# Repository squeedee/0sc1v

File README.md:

# 0sc1v
Turn the fader board from a Yamaha 01v mixer into a compact OSC controller

The [Yamaha 01v](https://usa.yamaha.com/files/download/other_assets/0/320870/01VE.pdf) was my favorite digital mixer of the 90s.
However I recently upgraded, to the [X-Air Xr-18 by Behringer](https://www.musictribe.com/Categories/Behringer/Mixers/Digital/XR18/p/P0BI8).
The XR-18 is so cheap, does so much, and I chose it based on certain criteria:

1. 24bit for headroom, the 16bit 01v made me work too hard up front
2. Lots of digital in/outs to my PC. I would have been happy with 8/8, but the XR-18 comes with 18/18
3. Physical controls

And it's the last point that makes the XR-18 sad for me, I like having physical faders. So this project is all about using
the motorized faders of my ailing 01v as a Fader Controller for the XR-18 (and everything else)

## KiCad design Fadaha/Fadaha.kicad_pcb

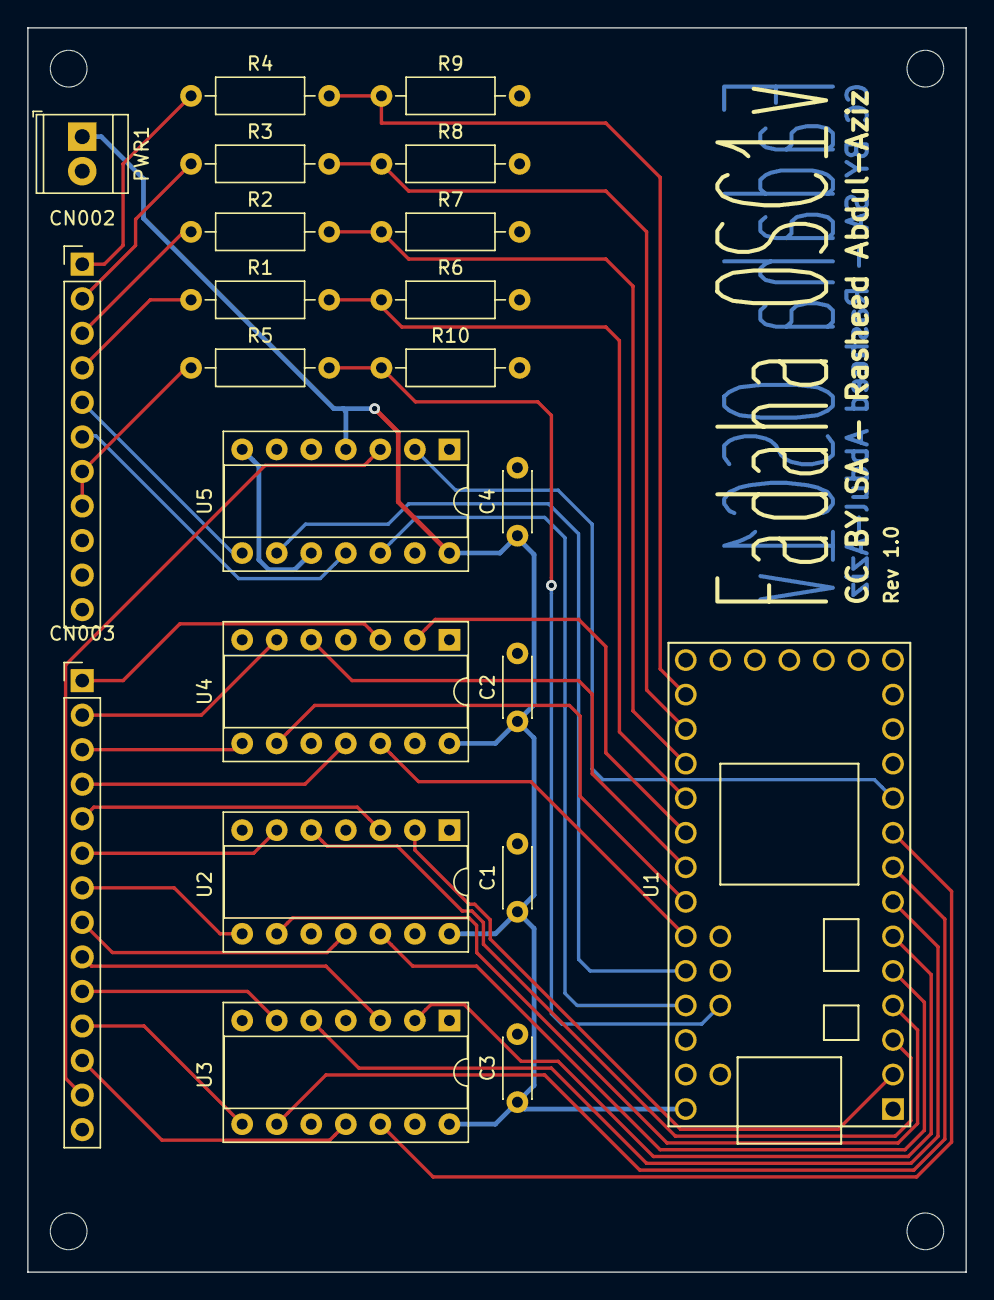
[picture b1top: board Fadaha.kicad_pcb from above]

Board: 2 copper layers, 69.0 x 91.5 mm, 23 parts (0 on the bottom side), 42 nets.

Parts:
C1, C2, C3, C4: 100nf; C_Disc_D4.3mm_W1.9mm_P5.00mm
CN002: 11 pin header; PinHeader_1x11_P2.54mm_Vertical
CN003: 14 pin header; PinHeader_1x14_P2.54mm_Vertical
GND: MountingHole_2.7mm_M2.5
PWR1: Screw_Terminal_01x02; TerminalBlock_TE_282834-2_1x02_P2.54mm_Horizontal
R1, R2, R3, R4, R5: 11k; R_Axial_DIN0207_L6.3mm_D2.5mm_P10.16mm_Horizontal
R6, R7, R8, R9, R10: 20k; R_Axial_DIN0207_L6.3mm_D2.5mm_P10.16mm_Horizontal
U1: Teensy3.2; Teensy30_31_32_LC-custom
U2, U3, U4, U5: 74125; DIP-14_W7.62mm_Socket

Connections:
/Faders/AREF: R5.2, R10.1, U1.35
/Faders/F0: R4.2, R9.1, U1.21
/Faders/F1: R3.2, R8.1, U1.22
/Faders/F2: R2.2, R7.1, U1.23
/Faders/F3: R1.2, R6.1, U1.24
/Faders/FINT0: CN002.1, R4.1
/Faders/FINT1: CN002.2, R3.1
/Faders/FINT2: CN002.3, R2.1
/Faders/FINT3: CN002.4, R1.1
/Faders/FSEL0: U1.29, U5.9
/Faders/FSEL1: U1.30, U5.12
/Motor Control/BANK0: U1.25, U4.2
/Motor Control/BANK1: U1.26, U4.5
/Motor Control/BANK2: U1.27, U4.9
/Motor Control/BANK3: U1.28, U4.12
/Motor Control/M0_A: U1.2, U2.2
/Motor Control/M0_B: U1.3, U2.5
/Motor Control/M1_A: U1.4, U2.9
/Motor Control/M1_B: U1.5, U2.12
/Motor Control/M2_A: U1.6, U3.2
/Motor Control/M2_B: U1.7, U3.5
/Motor Control/M3_A: U1.8, U3.9
/Motor Control/M3_B: U1.9, U3.12
/Motor Control/_RESET: U1.10, U5.2
GND: C1.2, C2.2, C3.2, C4.2, CN002.9, CN002.10, CN002.11, CN003.14, PWR1.2, R6.2, R7.2, R8.2, R9.2, R10.2, U1.1, U1.17, U1.32, U2.1, U2.4, U2.7, U2.10, U2.13, U3.1, U3.4, U3.7, U3.10, U3.13, U4.1, U4.4, U4.7, U4.10, U4.13, U5.1, U5.5, U5.7, U5.10, U5.13
unnamed: CN002.5, U5.8
unnamed: CN002.6, U5.11
unnamed: CN002.7, CN002.8, R5.1
unnamed: CN003.1, U4.3
unnamed: CN003.2, U4.6
unnamed: CN003.3, U4.8
unnamed: CN003.4, U4.11
unnamed: CN003.5, U2.3
unnamed: CN003.6, U2.6
unnamed: CN003.7, U2.8
unnamed: CN003.8, U2.11
unnamed: CN003.9, U3.3
unnamed: CN003.10, U3.6
unnamed: CN003.11, U3.8
unnamed: CN003.12, U3.11
unnamed: CN003.13, U5.3
VCC: C1.1, C2.1, C3.1, C4.1, PWR1.1, U1.33, U2.14, U3.14, U4.14, U5.4, U5.14

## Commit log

2019-02-22 Import existing work.
2019-02-22 make arduino IDE see the ino file
2019-02-22 trialling platformio
2019-02-24 Add motor support
2019-02-24 motor braking test

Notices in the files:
Fadaha/Fadaha.kicad_pcb:
CC BY SA - Rasheed Abdul-Aziz
